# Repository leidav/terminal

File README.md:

terminal
========
A simple serial terminal

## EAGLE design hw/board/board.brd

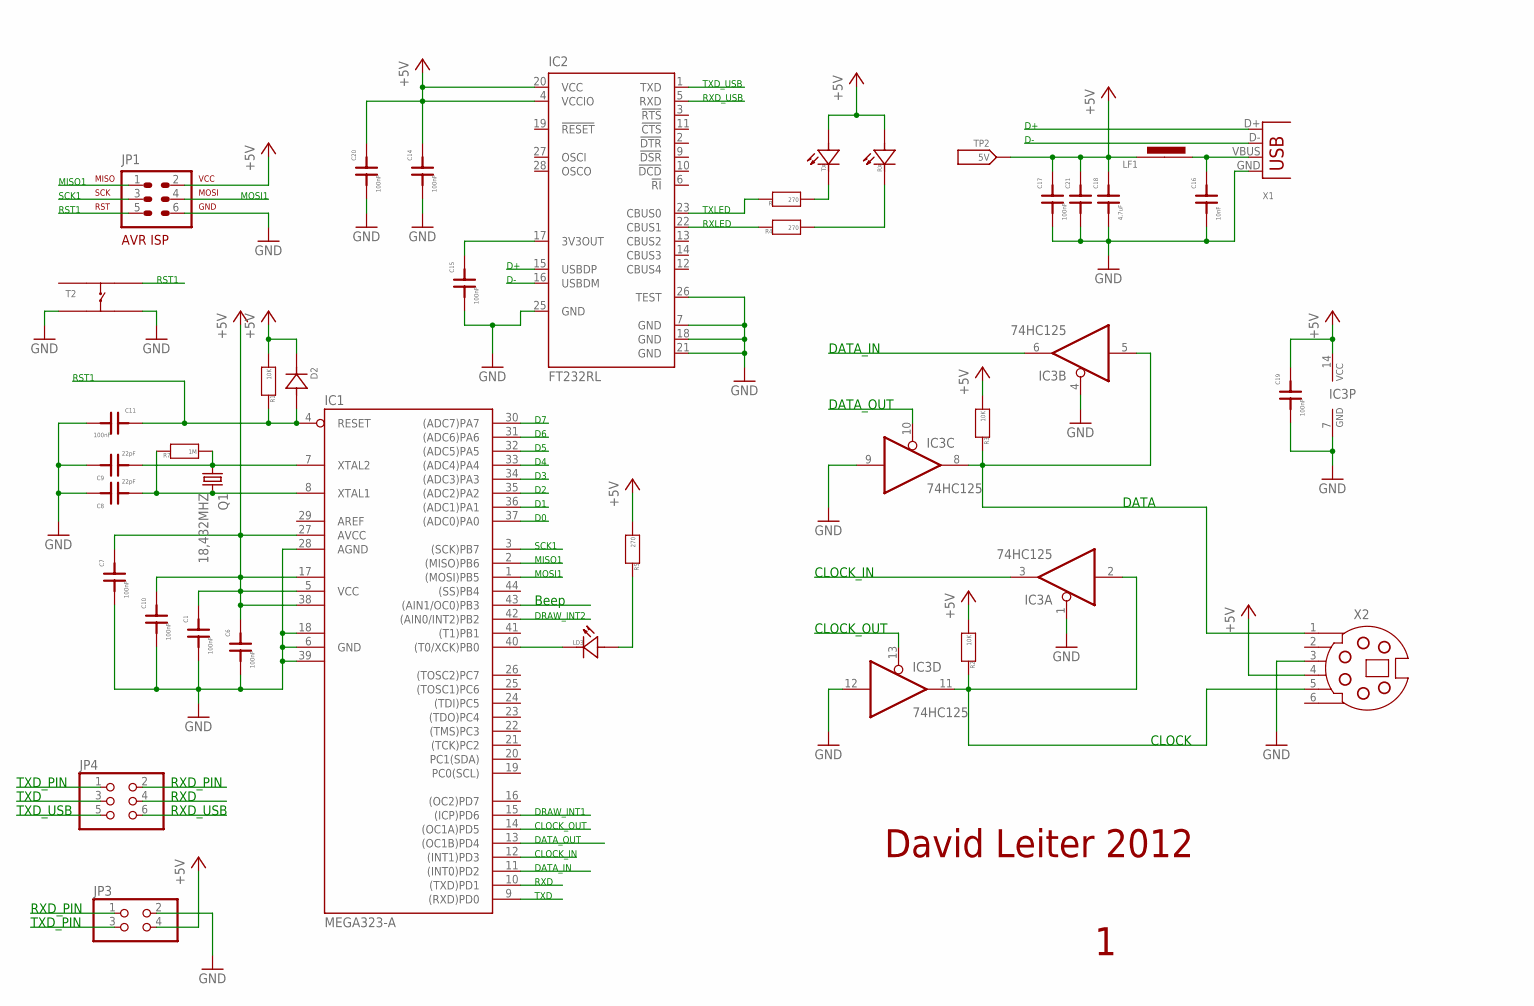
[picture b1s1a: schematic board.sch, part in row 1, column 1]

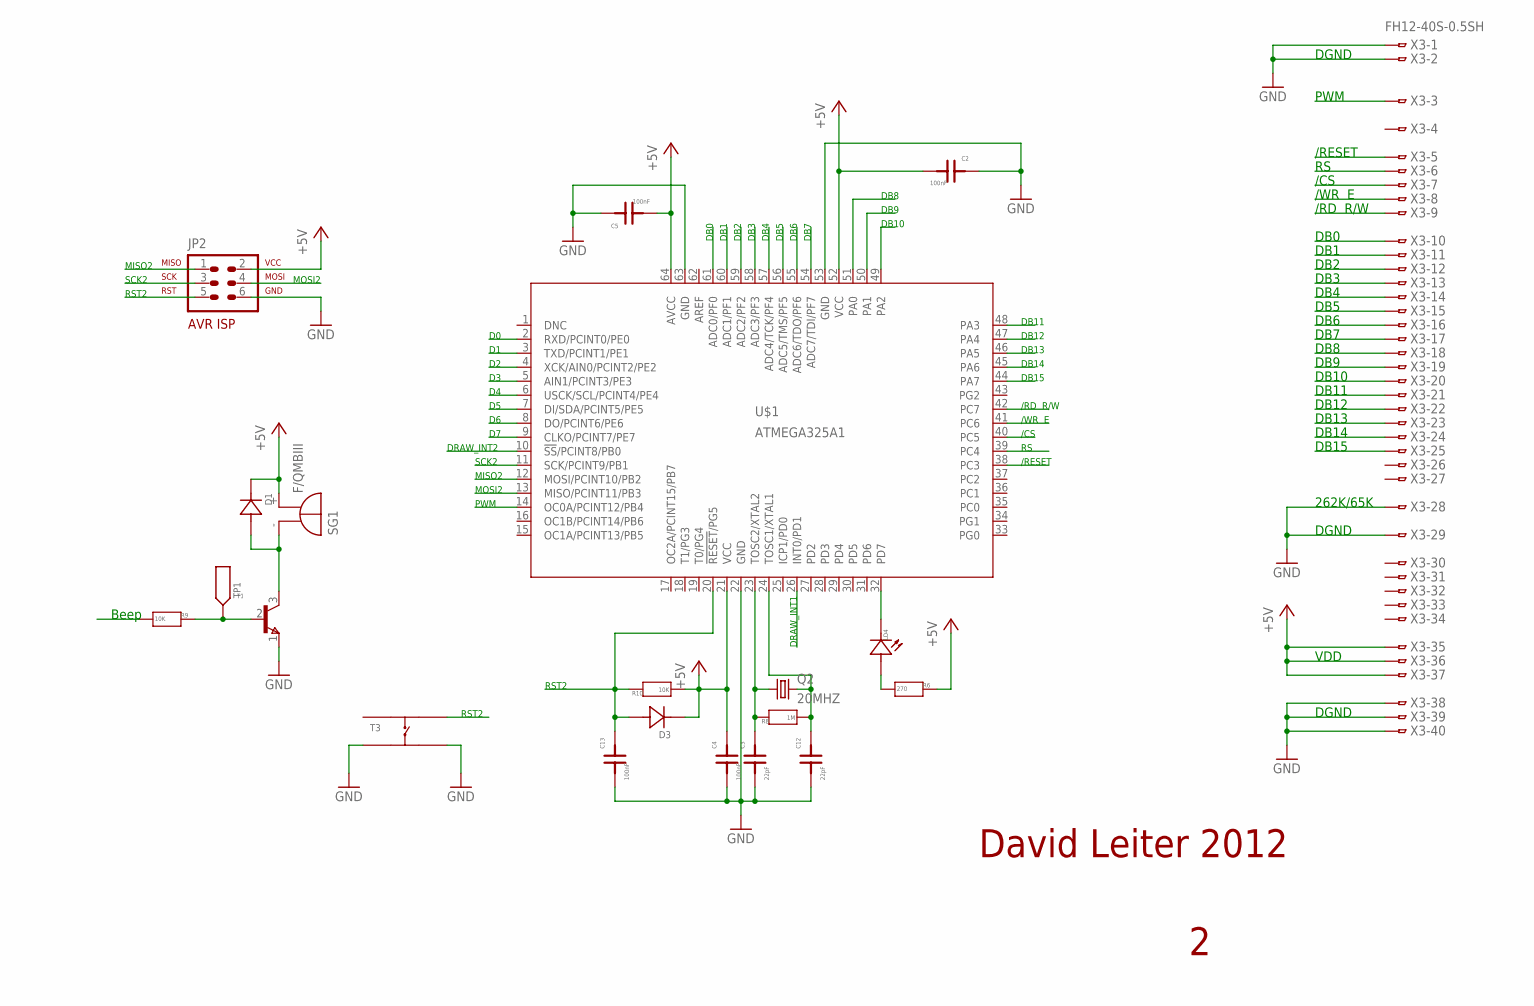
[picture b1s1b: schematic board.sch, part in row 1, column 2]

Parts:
C1, C2, C4, C5, C6, C7, C10, C11, C13, C14, C15, C17, C19, C20: 100nF; 0805F
C3, C8, C9, C12: 22pF; 0805F
C16: 10nF; 0805F
C18: 4,7uF; 0805F
C21: C1; 0805F
D1, D2, D3: DSOD80; SOD-80
IC1: MEGA323-A; TQFP44
IC2: FT232RL; SSOP28
IC3: 74HC125; SO14
JP1: ISP1; AVR-ISP-6
JP2: ISP2; AVR-ISP-6
JP3: PINHD-2X2/90; 2X02/90
JP4: PINHD-2X3; 2X03
LD3, LD4: LEDSMD; 0805LED
LF1: FERRIT0805; 0805
Q1: 18,432MHZ; HC49UP
Q2: 20MHZ; HC49UP
R, R4, R5, R6: 270; 0805
R1, R2, R3, R9, R10: 10K; 0805
R7, R8: 1M; 0805
RX: LEDSMD; 0805LED
SG1: F/QMBIII
T1: BC817; SOT-23
T2, T3: TASTERSMD; TASTE_SMD
TP1: TESTPOINT
TP2: 5V; TESTPOINT
TX: LEDSMD; 0805LED
U$1: ATMEGA325A1; TQFP64
X1: USB-B-H
X2: SSV-G06; SSV-BC06
X3: FH12-40S-0.5SH

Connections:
+5V: C1.2, C2.1, C4.2, C5.1, C6.2, C7.2, C10.2, C14.2, C17.2, C18.2, C19.2, C20.2, C21.2, D1.1 (K), D2.1 (K), D3.1 (K), IC1.5 (VCC), IC1.17 (VCC1), IC1.27 (AVCC), IC1.38 (VCC2), IC2.4 (VCCIO), IC2.20 (VCC), IC3.14 (VCC), JP1.2, JP2.2, JP3.4, LF1.1, R1.1, R2.1, R3.1, R5.1, R6.2, R10.1, RX.A (2), SG1.+ (-), TP2.P$1, TX.A (2), U$1.21 (VCC), U$1.52 (VCC), U$1.64 (AVCC), X2.4, X3.35, X3.36, X3.37
/CS: U$1.40 (PC5), X3.7
/RD: U$1.42 (PC7), X3.9
/RESET: U$1.38 (PC3), X3.5
/WR: U$1.41 (PC6), X3.8
BEEP: IC1.43 ((AIN1/OC0)PB3), R9.1
CLOCK: IC3.2 (I), IC3.11 (O), R2.2, X2.5
CLOCK_IN: IC1.12 ((INT1)PD3), IC3.3 (O)
CLOCK_OUT: IC1.14 ((OC1A)PD5), IC3.13 (OE)
D0: IC1.37 ((ADC0)PA0), U$1.2 (RXD/PCINT0/PE0)
D1: IC1.36 ((ADC1)PA1), U$1.3 (TXD/PCINT1/PE1)
D2: IC1.35 ((ADC2)PA2), U$1.4 (XCK/AIN0/PCINT2/PE2)
D3: IC1.34 ((ADC3)PA3), U$1.5 (AIN1/PCINT3/PE3)
D4: IC1.33 ((ADC4)PA4), U$1.6 (USCK/SCL/PCINT4/PE4)
D5: IC1.32 ((ADC5)PA5), U$1.7 (DI/SDA/PCINT5/PE5)
D6: IC1.31 ((ADC6)PA6), U$1.8 (DO/PCINT6/PE6)
D7: IC1.30 ((ADC7)PA7), U$1.9 (CLKO/PCINT7/PE7)
D+: IC2.15 (USBDP), X1.D+
D-: IC2.16 (USBDM), X1.D-
DATA: IC3.5 (I), IC3.8 (O), R3.2, X2.1
DATA_IN: IC1.11 ((INT0)PD2), IC3.6 (O)
DATA_OUT: IC1.13 ((OC1B)PD4), IC3.10 (OE)
DB0: U$1.61 (ADC0/PF0), X3.10
DB1: U$1.60 (ADC1/PF1), X3.11
DB2: U$1.59 (ADC2/PF2), X3.12
DB3: U$1.58 (ADC3/PF3), X3.13
DB4: U$1.57 (ADC4/TCK/PF4), X3.14
DB5: U$1.56 (ADC5/TMS/PF5), X3.15
DB6: U$1.55 (ADC6/TDO/PF6), X3.16
DB7: U$1.54 (ADC7/TDI/PF7), X3.17
DB8: U$1.51 (PA0), X3.18
DB9: U$1.50 (PA1), X3.19
DB10: U$1.49 (PA2), X3.20
DB11: U$1.48 (PA3), X3.21
DB12: U$1.47 (PA4), X3.22
DB13: U$1.46 (PA5), X3.23
DB14: U$1.45 (PA6), X3.24
DB15: U$1.44 (PA7), X3.25
DRAW_INT1: IC1.15 ((ICP)PD6), U$1.26 (INT0/PD1)
DRAW_INT2: IC1.42 ((AIN0/INT2)PB2), U$1.10 (!SS!/PCINT8/PB0)
GND: C1.1, C2.2, C3.1, C4.1, C5.2, C6.1, C7.1, C8.2, C9.2, C10.1, C11.1, C12.1, C13.1, C14.1, C15.1, C16.1, C17.1, C18.1, C19.1, C20.1, C21.1, IC1.6 (GND), IC1.18 (GND1), IC1.28 (AGND), IC1.39 (GND2), IC2.7 (GND), IC2.18 (GND), IC2.21 (GND), IC2.25 (GND), IC2.26 (TEST), IC3.1 (OE), IC3.4 (OE), IC3.7 (GND), IC3.9 (I), IC3.12 (I), JP1.6, JP2.6, JP3.2, T1.1 (E), T2.B1, T2.B2, T3.B1, T3.B2, U$1.22 (GND), U$1.53 (GND), U$1.63 (GND), X1.GND, X2.3, X3.1, X3.2, X3.28, X3.29, X3.38, X3.39, X3.40
MISO1: IC1.2 ((MISO)PB6), JP1.1
MISO2: JP2.1, U$1.13 (MISO/PCINT11/PB3)
MOSI1: IC1.1 ((MOSI)PB5), JP1.4
MOSI2: JP2.4, U$1.12 (MOSI/PCINT10/PB2)
unnamed: IC1.40 ((T0/XCK)PB0), LD3.K (1)
unnamed: D1.2 (A), SG1.- (+), T1.3 (C)
unnamed: C8.1, IC1.8 (XTAL1), Q1.2, R7.2
unnamed: C9.1, IC1.7 (XTAL2), Q1.1, R7.1
unnamed: LD3.A (2), R5.2
unnamed: C3.2, Q2.1, R8.2, U$1.23 (TOSC2/XTAL2)
unnamed: IC2.22 (CBUS1), R4.2
unnamed: R9.2, T1.2 (B), TP1.P$1
unnamed: LD4.K (1), U$1.32 (PD7)
unnamed: C15.2, IC2.17 (3V3OUT)
unnamed: LD4.A (2), R6.1
unnamed: R.1, TX.K (1)
unnamed: C12.2, Q2.2, R8.1, U$1.24 (TOSC1/XTAL1)
unnamed: IC2.23 (CBUS0), R.2
unnamed: R4.1, RX.K (1)
PWM: U$1.14 (OC0A/PCINT12/PB4), X3.3
RS: U$1.39 (PC4), X3.6
RST1: C11.2, D2.2 (A), IC1.4 (RESET), JP1.5, R1.2, T2.A2
RST2: C13.2, D3.2 (A), JP2.5, R10.2, T3.A2, U$1.20 (!RESET!/PG5)
RXD: IC1.10 ((TXD)PD1), JP4.4
RXD_PIN: JP3.1, JP4.2
RXD_USB: IC2.5 (RXD), JP4.6
SCK1: IC1.3 ((SCK)PB7), JP1.3
SCK2: JP2.3, U$1.11 (SCK/PCINT9/PB1)
TXD: IC1.9 ((RXD)PD0), JP4.3
TXD_PIN: JP3.3, JP4.1
TXD_USB: IC2.1 (TXD), JP4.5
VBUS: C16.2, LF1.2, X1.VBUS

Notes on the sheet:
MISO1
SCK1
MOSI1
SCK2
MISO2
MOSI2
RST1
RST2
DATA_IN
DATA_OUT
CLOCK_OUT
CLOCK_IN
DATA
CLOCK
RXD
TXD
RXD_USB
TXD_USB
DRAW_INT1
DRAW_INT2
TXLED
RXLED
David Leiter 2012
PWM
/RESET
/CS
/WR E
/RD R/W
DB0
DB1
DB2
DB3
DB4
DB5
DB6
DB7
DB8
DB9
DB10
DB11

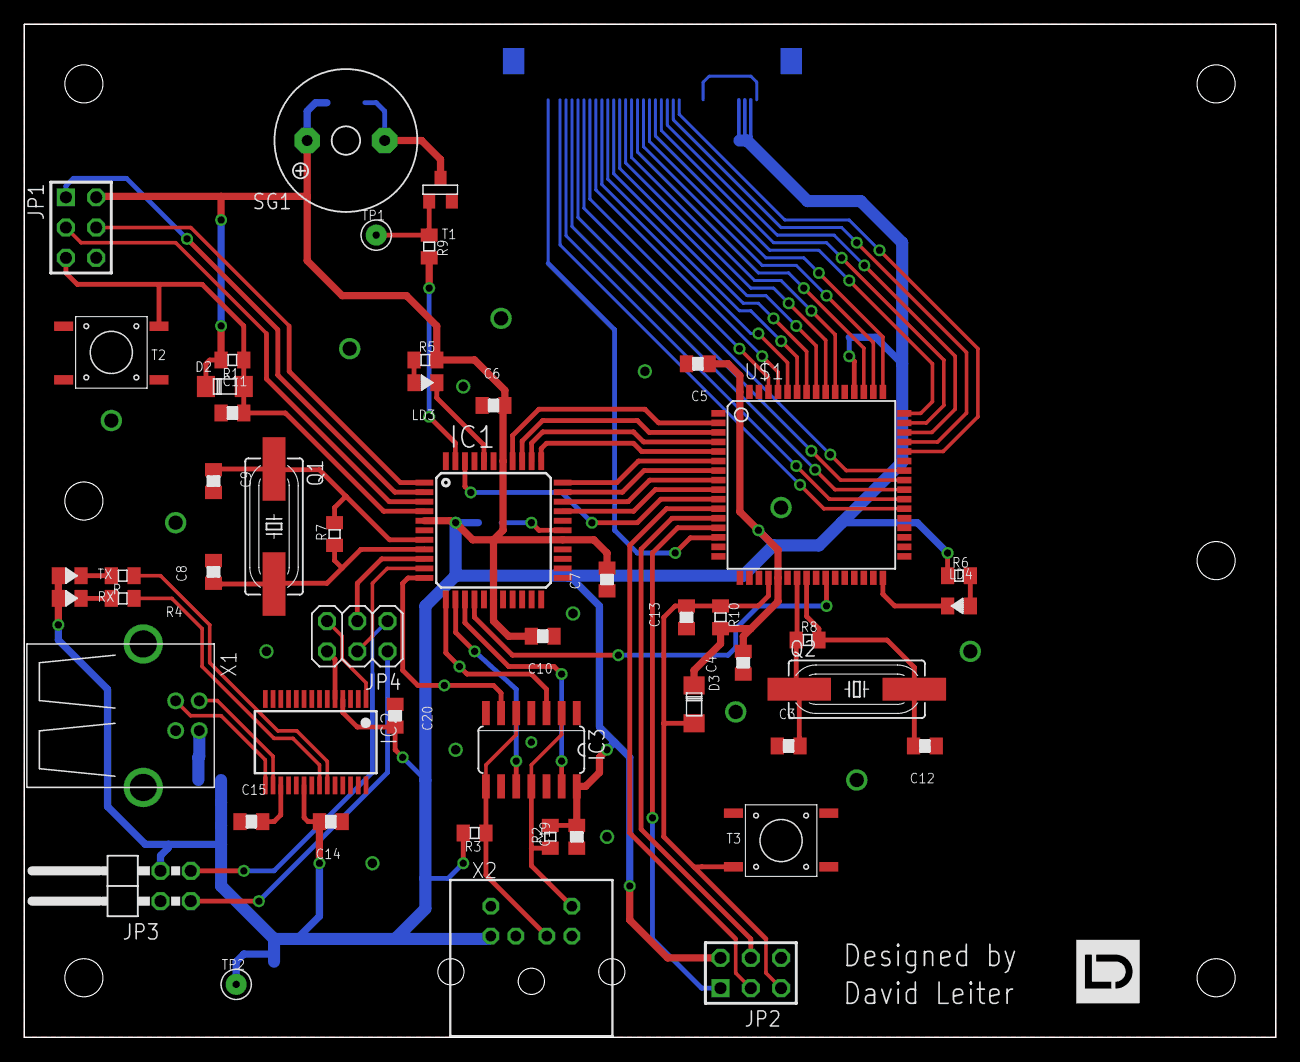
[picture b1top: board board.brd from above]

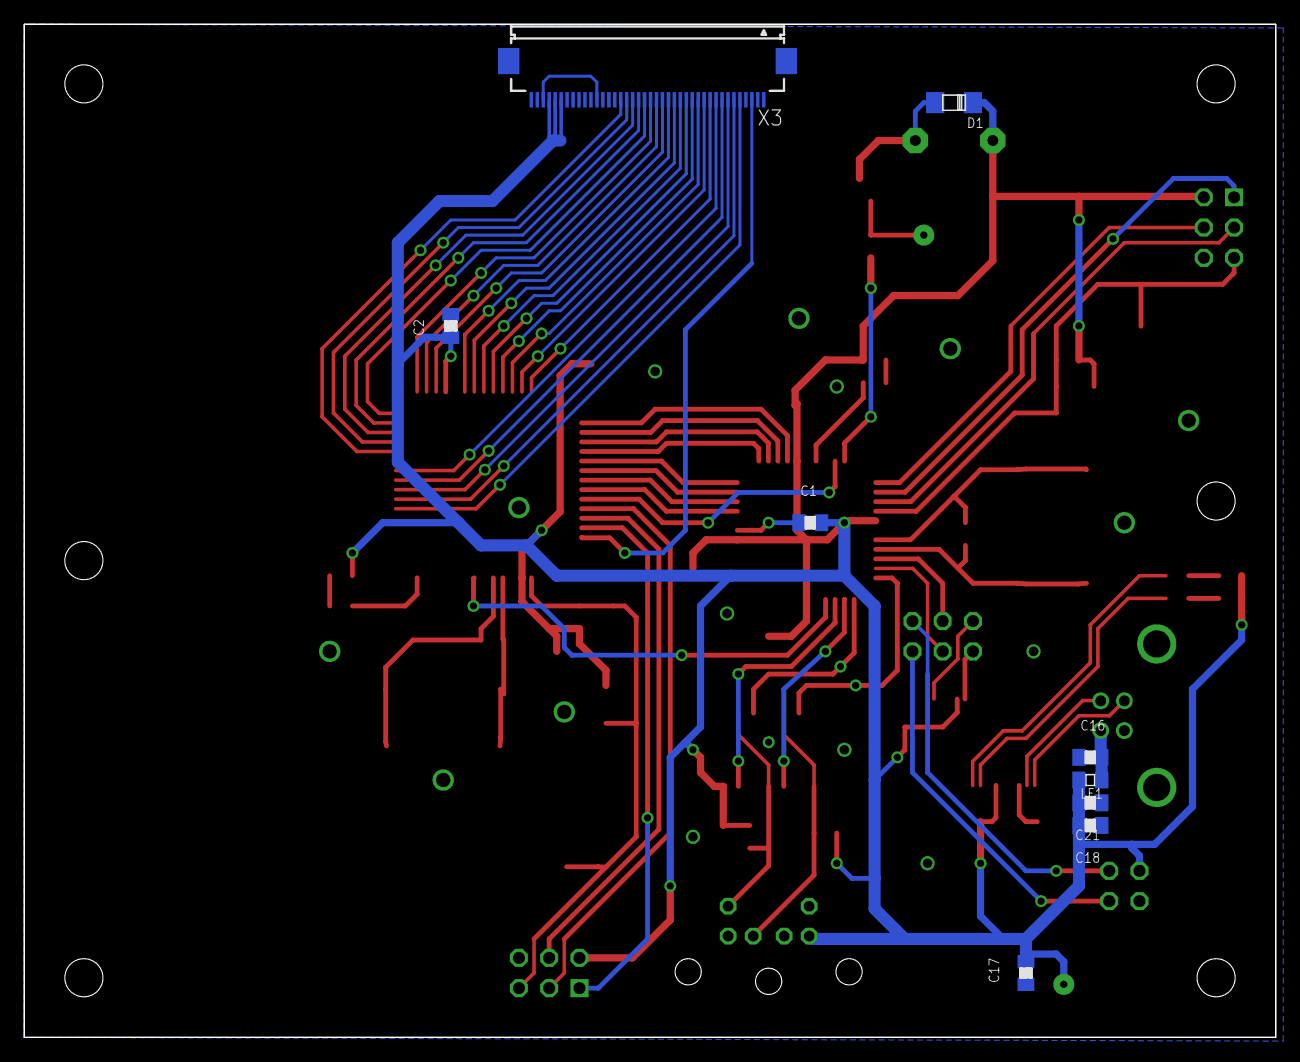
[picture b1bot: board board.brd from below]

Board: 2 copper layers, 105.0 x 85.0 mm, 59 parts (9 on the bottom side), 73 nets.

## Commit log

2016-05-09 add SRC variable to makefiles
2016-05-09 fix makefiles and add initial parser support
2017-10-27 backup
